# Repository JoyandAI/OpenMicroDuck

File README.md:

# OpenMicroDuck

**一只完全开源的 25cm 双足机器人**

[English](README_en.md) | [中文](README.md)

---

## 这是什么

OpenMicroDuck 是一个**完全开源**的双足机器人平台：一只 25cm 高、不到 1kg 的小鸭子，15 个自由度，能走、会转头、能发声，可以运行强化学习策略。

本项目受** Hugging Face / Pollen Robotics 的 MicroDuck**的启发——感谢他们把这只小鸭子带到世界面前，让全球开发者看到双足机器人可以如此可爱而触手可及；也感谢他们以开放的态度公开训练生态，让我们得以站在他们的肩膀上继续向前。在 MicroDuck 的基础上，我们将把复现过程的硬件图纸、PCB、BOM、软件栈、训练环境——全部公开发布。

它是我们对"技术平权"的一次实践，也是对 MicroDuck 的致谢。

## 当前进展

飞特 HD-1910 的 BAM 执行器参数，参考陆吾智能按 STS3215 执行器标定的M6参数。在仿真强化学习项目 [microduck_rl](https://github.com/JoyandAI/microduck_rl/tree/develop/vendor/bam/bam/params/hd1910) 中已经更新。

### 最新视频

[OpenMicroduck--试一下我新的“鞋子”](https://www.bilibili.com/video/BV1bcxh6PE4x/)

[OpenMicroDuck-展示一下国庆训练效果](https://www.bilibili.com/video/BV1hHHX6sEhS/)

基础模型已经放出权重，在 [policies](policies/) 目录中。五个 ONNX 都是 HD-1910 上可部署的策略，观测 `[1,61]`、动作 `[1,14]`，归一化已经烘进图里。部署参数和槽位分工见 [policies/README.md](policies/README.md)。

| 模型  | 文件                        | 做什么                                            |
| --- | ------------------------- | ---------------------------------------------- |
| 行走  | `OpenMD_walk.onnx`        | 按速度指令走路（`openmd_velocity`，迭代 9999）。摇杆有速度时走这一路。 |
| 站立  | `OpenMD_stand.onnx`       | 速度为零时站立（`openmd_velstand`，迭代 17500）。           |
| 捡东西 | `OpenMD_ground_pick.onnx` | 俯身去捡地上的东西（迭代 3000，踝关节增益 0.37 已写进图里）。           |
| 右踢  | `OpenMD_kick_right.onnx`  | 右脚踢球，时长 0.5 秒。                                 |
| 翻滚  | `OpenMD_roulade.onnx`     | 前滚翻一周，时长 1 秒。                                  |

### 预部署镜像

适配 Radxa Zero 3W，已经安装 microduck 运行时程序的系统我们已经压缩打包成镜像，希望可以节省大家配置环境的时间。

镜像路径：[Openmicroduck Radxa Zero 3W镜像](https://pan.baidu.com/s/15vAhpStkQ0C7q6i9n2H0tQ?pwd=7yzd)

## 交流群

## BOM

规格、数量、版本差异与结构件清单见 **[docs/bom.md](docs/bom.md)**。

| 器件                | 型号                   | 规格                                          | 数量   | 参考单价和链接                                                                                                                                                                                                                 |
| ----------------- | -------------------- | ------------------------------------------- | ---- | ----------------------------------------------------------------------------------------------------------------------------------------------------------------------------------------------------------------------- |
| 舵机                | **飞特 HD-1910-C001**  | 恒力空心杯舵机，4~8.4V，堵转扭矩 12kg·cm                 | 15   | [118](https://item.taobao.com/item.htm?id=1014620157895&mi_id=0000xBjtqiNSYJUq7QGMPpbYwmNEROqnEVZwYJWi5M4hP3Q&skuId=6133422044091&spm=a21n57.shop_search.0.0.18263d65wuqx4I)                                            |
| 主控                | **Radxa ZERO 3W**    | RK3566, 2GB RAM，带WiFi, 无eMMC板, 带排针版         | 1    | [309](https://item.taobao.com/item.htm?id=763812025816&mi_id=0000uT5x0cTXxWeiB08JXVyTWI8UsD7hlB5D9f1engmhabY&spm=tbpc.boughtlist.suborder_itemtitle.1.2b562e8dNOWpmj&skuId=6066053424678)                               |
| SD卡               | MicroSD/TF卡          | 64GB，A1以上                                   | 1    | 60~100                                                                                                                                                                                                                  |
| Zero Robot HAT转接板 |                      | 兼容AMP2.0 3P插口，可接飞特HD1910。扬声器、麦克风插口换成XH-1.25 | 1    | [228](https://item.taobao.com/item.htm?abbucket=0&id=1090876838510&mi_id=0000ZS5hbUuCFijZNBh6Wm1foqfNFOfbMtdJPq5ofUGb8g8&ns=1&skuId=6311561534333&spm=a21xtw.29978516.product_shelf.11.7a1573ecGsriLO&xxc=taobaoSearch) |
| IMU_to_servo转接板   |                      | LSM6DSV16X，带AMP2.0-3P插口，供电转接一体              | 1    | [158](https://item.taobao.com/item.htm?abbucket=0&id=1090873750118&mi_id=0000GbQT_tQe9YyNB1BGCyB_worUMn9XTHC7XOhnoTa6T74&ns=1&skuId=6311743311265&spm=a21xtw.29978516.product_shelf.12.7a1573ecGsriLO&xxc=taobaoSearch) |
| 摄像头模组             | IMX219带FPC排线         | 800万像素                                      | 1    |                                                                                                                                                                                                                         |
| 结构件               | PLA[+TPU] FDM 3D打印   | 有条件的话，脚垫可选用TPU打印或脚底加硅胶垫                     | 1    | -                                                                                                                                                                                                                       |
| 轴承                | 6700K                | 10 x 15 x 3                                 | 3    | [2](https://item.taobao.com/item.htm?id=1084278550250&mi_id=0000IFo09JQwrF2qO5b7uhalH5jN7IxahG44rLmmvDEeCC8&skuId=6303412790720&spm=a21xtw.29978518.0.0&xxc=shop)                                                       |
| 轴承                | ET2216               | 16 x 22 x 4                                 | 11 * | [3.5](https://item.taobao.com/item.htm?id=1084278550250&mi_id=0000IFo09JQwrF2qO5b7uhalH5jN7IxahG44rLmmvDEeCC8&skuId=6303412790721&spm=a21xtw.29978518.0.0&xxc=shop)                                                     |
| 紧固件               | 螺丝                   | M2自攻                                        | 若干   |                                                                                                                                                                                                                         |
| 麦克风               | 6050驻极体麦克风           |                                             | 2    |                                                                                                                                                                                                                         |
| 扬声器               | 3525腔体喇叭             |                                             | 1    |                                                                                                                                                                                                                         |
| 电池                | 7.4V 3500mAh 2S 锂电池组 | 18650 2串，放电倍率2C，XH2.54 2P公头                 | 1    | [48.9](https://item.taobao.com/item.htm?id=585852453584&mi_id=0000zeSmMUkUHskP6x88HRHh6m6PNRO0ZnSVYlrEaGHAW4g&spm=tbpc.boughtlist.suborder_itemtitle.1.34c22e8dbHwgTb)                                                  |

 ET2216 按真正承重、并降低摩擦的关节计 11 只。另外 10 处关节留了轴承位，但没有起到支撑旋转、降低摩擦的作用。若打印件沿用 Pollen 原版结构，并要和原版 Microduck 的结构仿真对齐，可按一整套 14 只轴承采购。

### 研发辅助材料

以下是研发调试材料，不是每台机器人必须的BOM

| 器件         | 型号                         | 规格                            | 数量  | 参考单价和链接 |
| ---------- | -------------------------- | ----------------------------- | --- | ------- |
| 舵机驱动板      | 微雪串口总线舵机驱动板                | TypeC接口                       | 1   |         |
| 舵机电源适配器    | 7.5V舵机电源适配器                | 7.5V6A，DC5.5*2.1插头            | 1   | -       |
| 主控电源适配器    | PD直流电源适配器                  | 用TypeC口的PD电源适配器就可以，确认支持5V2A以上 | 1   | -       |
| 数据线        | USB TypeC->TypeA 或 双头TypeC | 0.5m~1.5m                     | 1   |         |
| MicroHDMI线 | MicroHDMI->HDMI线           | ~1.5m                         | 1   |         |
| 读卡器        | MicroSD卡读卡器                | USB 2.0够用，如果笔记本已经有就不需要了       | 1   |         |

## 整机架构

软件与 Microduck 同一条回路：离线 PPO 训出 ONNX，板上 **50 Hz** 执行，契约 **观测 61 维 → 动作 14 维**。硬件换成可公开打样的国产件；换舵机必须重训，官方 ONNX 不能当即插即用步态。

选型对照、舵机连线、进程与控制环见 **[docs/README.md](docs/README.md)**（[架构](docs/architecture.md) · [主控](docs/main_controller.md) · [舵机](docs/servo.md)）。

## 路线图

| 里程碑 | 时间        | 目标                     | 进度 |
| --- | --------- | ---------------------- |
| M1  | 2026-09   | 整机组装，RL 行走验证，桌面调试版确定   | 已完成 |
| M2  | 2026-10   | 整机集成版确定，中英双语教程上线       | 整机集成版完成，教程整理中 |
| M3  | 2026-11 ~ | 量产版投产，生态放大：技能包、兼容性持续优化 | ID设计进行中 |

开源项目不拼小批量台数，拼的是复现成功率与开发者体验。每个里程碑公开评审，测试数据与问题清单全量开放。

## 如何参与

任何程度的参与都有意义：

1. **关注** —— Star 本仓库，加入社区（Discord / B 站 / 微信群），见证并传播进展
2. **文档** —— 中英双语教程写作、文档翻译
3. **复现** —— 打印、组装，把公差与干涉问题提 Issue；复现数据是开源硬件最硬的通货
4. **创作** —— 技能包、外观二创、训练管线改进
5. **共建** —— 核心模块 PR，进入维护者委员会，共同决定技术方向

贡献指南见 `CONTRIBUTING.md`（待发布）。

## 为什么做这个项目

**让门槛再低一点。** 双足机器人的核心技术并没有想象中遥远，但一套进口舵机动辄数千元、关键结构闭源、教程零散——把太多人挡在了门外。我们把每个环节拆开、验证、用高性价比的国产供应链重新实现，然后把一切公开：主控只要求 RK3566 同级算力，电池组安全、可拆解，结构件一台 3D 打印机就能做出来。

**让生态再大一点。** 我们希望更多供应链厂商参与进来——舵机、主控、电池、3D 打印与注塑结构件。兼容性矩阵公开，任何厂商的同类器件都可以来适配。竞争发生在开放的标准上，受益的是整个生态。

**让创意再多一点。** 一只鸭子能做什么，不该由我们定义。换一个皮肤甚至换一种形态、写一个新技能、改一套步态、接一颗传感器——我们期待看到更多开发者的二创、以及我们根本想象不到的玩法。你创造的不只是一台机器鸭，而是下一个有意思、有价值产品的起点。

## 许可证

| 内容           | 许可证        |
| ------------ | ---------- |
| 硬件图纸、PCB、BOM | CERN-OHL-S |
| 软件栈、训练环境     | Apache-2.0 |
| 教程与文档        | CC BY-SA   |

## 致谢

本项目受 Hugging Face / Pollen Robotics 的 MicroDuck启发，并复用了其公开的训练生态。再次感谢 MicroDuck 团队的开创性工作与开放精神——没有他们，就没有这个项目。OpenMicroDuck 是独立的社区开源项目，与 Hugging Face、Pollen Robotics 无隶属关系。

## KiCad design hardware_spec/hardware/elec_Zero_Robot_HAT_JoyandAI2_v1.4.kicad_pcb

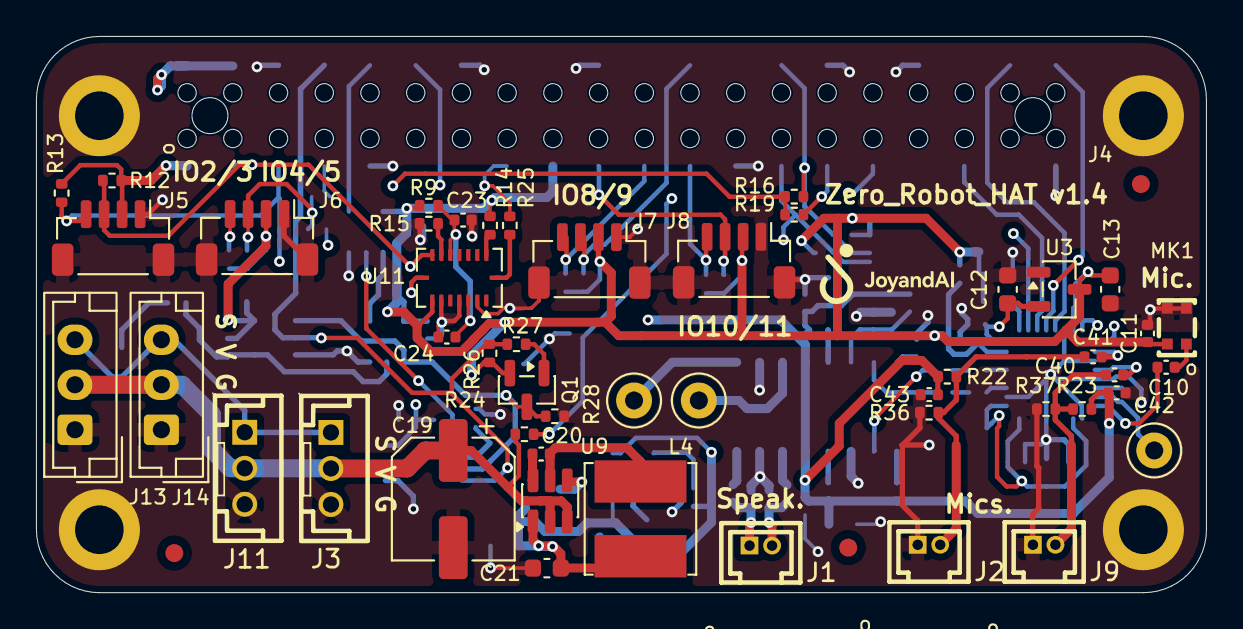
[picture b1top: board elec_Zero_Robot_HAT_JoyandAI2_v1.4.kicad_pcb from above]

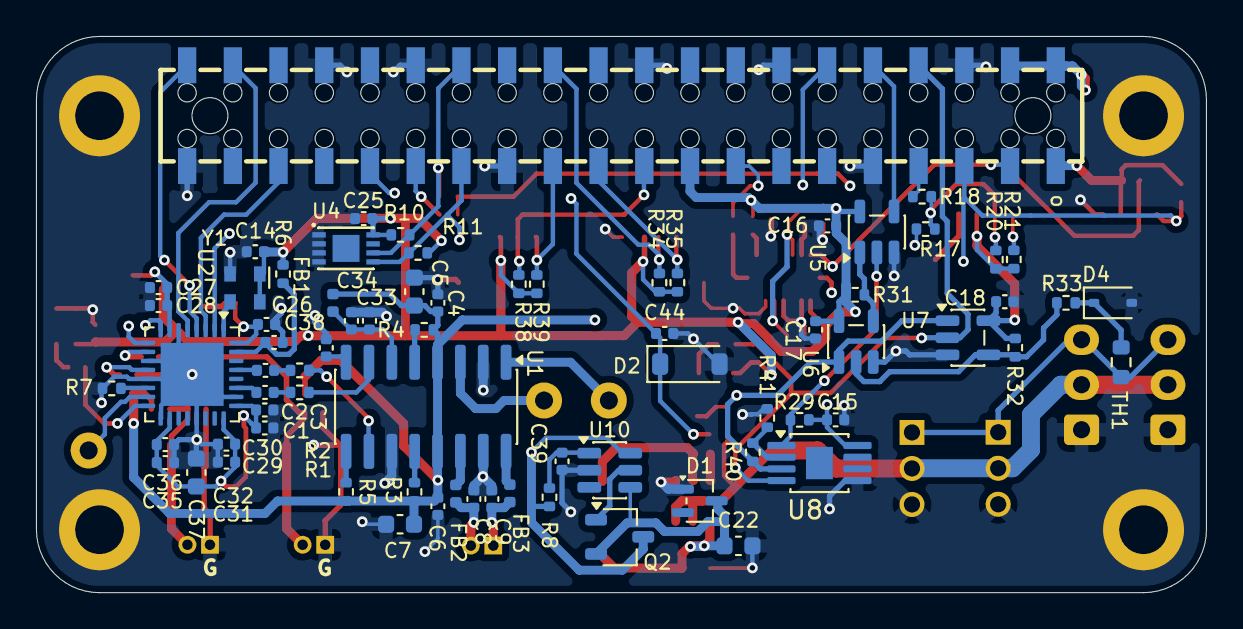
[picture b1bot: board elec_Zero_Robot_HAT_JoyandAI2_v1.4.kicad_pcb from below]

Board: 4 copper layers, 65.0 x 30.9 mm, 126 parts (73 on the bottom side), 69 nets.

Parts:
C1, C2, C3, C4, C6, C10, C27, C29, C31, C33, C35, C40, C41, C42, C43: 1u; C_0402_1005Metric
C5, C7, C12, C13, C37: 10u; C_0603_1608Metric
C8, C9: 220n; C_0402_1005Metric
C11, C14, C15, C16, C17, C18, C26, C28, C30, C32, C36, C38: 100n; C_0402_1005Metric
C19: 10u 63V; CP_Elec_6.3x7.7
C20: 100n 50V; C_0402_1005Metric
C21, C22: 22u 6V3; C_0603_1608Metric
C23, C24, C39: 100n 6V3; C_0402_1005Metric
C25: DNP-100n; C_0402_1005Metric
C34, C44: 10n; C_0402_1005Metric
D1: BAT54W; SOT-323_SC-70
D2: 3V3 Zener Diode; D_SOD-123
D4: 5V1; D_SOD-323
FB1: 1.3A 600R@100MHz; L_0402_1005Metric
FB2, FB3: 2A - 120R@100MHz; L_0402_1005Metric
FID1, FID2, FID3: DNP Fiducial; Fiducial_1mm_Mask2mm
H2: Logo HF 2025; Logo_HF_2025
J1, J2, J9: ZX-MX1.25-2PZZ; CONN-TH_2P-P1.25_MEGASTAR_ZX-MX1.25-2PZZ
J3, J11: A2007WV-3P; CONN-TH_A2007WV-3P
J4: Female Header 2x20 SMD; PinHeader_2x20_P2.54mm_Vertical_with_rasp_HAT_zero_SMD_conn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
J5, J6, J7, J8: JST SH; JST_SH_BM04B-SRSS-TB_1x04-1MP_P1.00mm_Vertical
J13, J14: Dynamixel-3; JST_EH_B3B-EH-A_1x03_P2.50mm_Vertical
L4: 6,8u 2A; L_Bourns_SRN6045TA
MK1: Microphone_MEMS; MIC-SMD_4P-L2.8-W1.9-P1.84-TL
Q1: MMBT3906; SOT-23
Q2: SI2312CDS-T1-GE3; TSOT-23
R1, R2, R6, R12, R13, R20, R21, R22, R23, R24, R26, R27, R29, R31, R32, R34, R35, R38, R39: 10k; R_0402_1005Metric
R3, R4, R5, R7, R9, R14, R15, R18, R19, R25, R33, R40: 0R; R_0402_1005Metric
R8: 100R; R_0402_1005Metric
R10, R11: DNP-10k; R_0402_1005Metric
R16, R17, R41: DNP-0R; R_0402_1005Metric
R28: 20k; R_0402_1005Metric
R36, R37: DNP-1M; R_0402_1005Metric
TH1: 100R thermistor; R_0603_1608Metric
TP2, TP3, TP4: TestPoint; TestPoint_Loop_D2.50mm_Drill1.0mm_LowProfile
U1: PAM8406D; SOIC-16_3.9x9.9mm_P1.27mm
U2: TLV320AIC3104IRHBR; VQFN-32-1EP_5x5mm_P0.5mm_EP3.5x3.5mm
U3: XC6206P182MR; SOT-23-3
U4: DNP-CAT24C32HU4; TDFN-8_L3.0-W2.0-P0.50-BL-EP
U5: 74LVC1G08; SOT-23-5
U6: SN74LVC1G125DBV; SOT-23-5
U7: SN74LVC1G126DBVR; SOT-23-5
U8: SIT3088E; MSOP-8-1EP_3x3mm_P0.65mm_EP1.5x1.8mm
U9: AP63205; TSOT-23-6
U10: LM5050-1; TSOT-23-6
U11: BMI088; Bosch_LGA-16_4.5x3mm_P0.5mm_LayoutBorder7x1y_ClockwisePinNu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
Y1: 12 MHz; Oscillator_SMD_Abracon_ASDMB-4Pin_2.5x2.0mm

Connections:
+1V8: C12.1, C26.2, U2.32 (DVDD), U3.2 (VO)
+3V3: C11.2, C13.1, C14.2, C15.2, C16.2, C17.2, C18.2, C25.2, C27.2, C28.2, C29.2, C30.2, C31.2, C32.2, C35.2, C36.2, C37.1, J4.1, J4.17, J5.2, J6.2, J7.2, J8.2, MK1.4 (+), Q1.2 (E), R6.1, R9.2, R10.1, R11.1, R12.1, R13.1, R14.1, R20.1, R21.1, R26.2, R29.1, R31.1, R32.1, R34.1, R35.1, R38.1, R39.1, U2.7 (IOVDD), U2.18 (DRVDD), U2.24 (DRVDD), U2.25 (AVDD), U3.3 (VI), U4.8 (VCC), U5.5 (VCC), U6.5 (VCC), U7.5 (VCC), U8.8 (VCC), U11.7 (PS), Y1.1 (Tri-State), Y1.4 (VDD)
+5V: C4.1, C5.1, C6.1, C7.1, C42.2, C43.2, FB1.2, J4.2, J4.4, Q2.3 (D), R3.2, R4.2, R5.2, R8.1, R22.2, R23.2, U1.4 (PVDDL), U1.13 (PVDDR), U10.6 (OUT)
+BATT: C19.1, J3.2, J11.2, J13.2, J14.2, R24.2, U9.2 (EN), U9.3 (IN)
/Schematic/Audio/ID_SC: J4.28, R10.2, R16.1, U4.6 (SCL)
/Schematic/Audio/ID_SD: J4.27, R11.2, R17.1, U4.5 (SDA)
/Schematic/Audio/IO_02: J4.3, J5.3, R12.2, U2.9 (SDA), U11.9 (SDI/SDA)
/Schematic/Audio/IO_03: J4.5, J5.4, R13.2, U2.8 (SCL), U11.8 (SCK/SCL)
/Schematic/Audio/IO_04: J4.7, R18.1
/Schematic/Audio/IO_05: J4.29, R19.1
/Schematic/Audio/IO_06: C44.1, D2.1 (K), J4.31, R24.1
/Schematic/Audio/IO_08: J4.24, J7.3, R34.2
/Schematic/Audio/IO_09: J4.21, J7.4, R35.2
/Schematic/Audio/IO_10: J4.19, J8.3, R38.2
/Schematic/Audio/IO_11: J4.23, J8.4, R39.2
/Schematic/Audio/IO_14: J4.8, R26.1, R27.1, U7.2, U8.4 (DI)
/Schematic/Audio/IO_15: J4.10, U5.4
/Schematic/Audio/IO_18: J4.12, U2.2 (BCLK)
/Schematic/Audio/IO_19: J4.35, U2.3 (WCLK)
/Schematic/Audio/IO_20: J4.38, U2.5 (DOUT)
/Schematic/Audio/IO_21: J4.40, U2.4 (DIN)
/Schematic/Audio/IO_22: J4.15, R25.1
/Schematic/Dynamixel/Dynamixel_dir: Q1.3 (C), R28.2, R40.1, U6.1, U7.1, U8.3 (DE)
GND: C3.1, C4.2, C5.2, C6.2, C7.2, C8.2, C9.2, C11.1, C12.2, C13.2, C14.1, C15.1, C16.1, C17.1, C18.1, C19.2, C21.2, C22.2, C23.2, C24.1, C25.1, C26.1, C27.1, C28.1, C29.1, C30.1, C31.1, C32.1, C33.2, C34.2, C35.1, C36.1, C37.2, C38.1, C39.2, C42.1, C43.1, C44.2, D1.1 (A), D2.2 (A), D4.2 (A), J2.1, J3.3, J4.6, J4.9, J4.14, J4.20, J4.25, J4.30, J4.34, J4.39, J4.MP (MountPin), J5.1, J5.MP (MountPin), J6.1, J6.MP (MountPin), J7.1, J7.MP (MountPin), J8.1, J8.MP (MountPin), J9.1, J11.3, J13.1, J14.1, MK1.2 (-), MK1.3 (-), R7.1, R15.1, R28.1, R36.1, R37.1, R41.1, U1.2 (PGNDL), U1.11 (GND), U1.15 (PGNDR), U2.6 (DVSS), U2.11 (MIC1LM/LINE1LM), U2.13 (MIC1RM/LINE1RM), U2.17 (AVSS1), U2.21 (DRVSS), U2.26 (AVSS2), U2.33 (EP), U3.1 (GND), U4.1 (A0), U4.2 (A1), U4.3 (A2), U4.4 (GND), U5.3 (GND), U6.3 (GND), U7.3 (GND), U8.5 (GND), U9.4 (GND), U10.2 (GND), U11.2 (GNDA), U11.4 (GNDA), U11.6 (GNDIO), Y1.2 (GND)
unnamed: C1.2, R1.1
unnamed: C2.2, R2.1
unnamed: C10.1, MK1.1 (-)
unnamed: C21.1, C22.1, D1.3 (K), L4.1, Q2.2 (S), U9.1 (FB), U10.4 (IN)
unnamed: D4.1 (K), R33.2, TH1.1
unnamed: C9.1, FB3.2, J1.1
unnamed: C8.1, FB2.2, J1.2
unnamed: C41.2, J2.2, R22.1, R36.2
unnamed: J6.3, R17.2, R18.2, R20.2
unnamed: J6.4, R16.2, R19.2, R21.2
unnamed: C40.2, J9.2, R23.1, R37.2
unnamed: J3.1, J11.1, J13.3, J14.3, TH1.2
unnamed: Q1.1 (B), R27.2
unnamed: Q2.1 (G), U10.5 (GATE)
unnamed: R31.2, U5.1, U6.4
unnamed: R32.2, R33.1, U6.2, U7.4
unnamed: TP3.1, U1.1 (+OUT_L)
unnamed: FB3.1, U1.16 (+OUT_R)
unnamed: TP4.1, U1.3 (-OUT_L)
unnamed: FB2.1, U1.14 (-OUT_R)
unnamed: R1.2, U1.7 (INL)
unnamed: R2.2, U1.10 (INR)
unnamed: R5.1, U1.9 (MODE)
unnamed: C33.1, C34.1, FB1.1, U1.6 (VDD)
unnamed: C3.2, U1.8 (VREF)
unnamed: R4.1, U1.5 (~MUTE)
unnamed: R3.1, U1.12 (~SHND)
unnamed: C1.1, U2.27 (LEFT_LOP)
unnamed: U2.1 (MCLK), Y1.3 (OUT)
unnamed: C41.1, U2.10 (MIC1LP/LINE1LP)
unnamed: C40.1, U2.12 (MIC1RP/LINE1RP)
unnamed: R7.2, U2.14 (MIC2L/LINE2L/MICDET)
unnamed: C10.2, U2.16 (MIC2R/LINE2R)
unnamed: TP2.1, U2.15 (MICBIAS)
unnamed: C2.1, U2.29 (RIGHT_LOP)
unnamed: C38.2, R6.2, U2.31 (~RESET)
unnamed: R29.2, U5.2, U8.1 (RO)
unnamed: R40.2, R41.2, U8.2 (~RE)
unnamed: C20.1, U9.6 (BST)
unnamed: C20.2, L4.2, U9.5 (SW)
unnamed: C39.1, R8.2, U10.1 (VS)
unnamed: R25.2, U11.16 (INT1)
unnamed: R14.2, U11.15 (SDO1)
unnamed: R15.2, U11.10 (SDO2)
unnamed: C23.1, C24.2, R9.1, U11.3 (VDD), U11.11 (VDDIO)
